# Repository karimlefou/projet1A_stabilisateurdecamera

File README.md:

# Projet 1A : Stabilisateur Brushless

**Équipe** : karim OUERFELLI + AMR  
**Encadrant** : M. Dumas

## 📌 Contexte
Stabilisation  d'un axe pour caméras légères (<1kg) utilisant des moteurs brushless.

## 🛠 Solution
- **Moteurs** : T-Motor MN3508  
- **Contrôle** : STM32 + IMU MPU-6050  
- **Algo** : PID temps-réel (<50ms)

## 🔗 Ressources
[Présentation](https://lien.canva) | [Rapport](https://lien.doc)

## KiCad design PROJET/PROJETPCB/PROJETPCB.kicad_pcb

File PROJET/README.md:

# PROJET
projet de 1 ére année à l'ensea

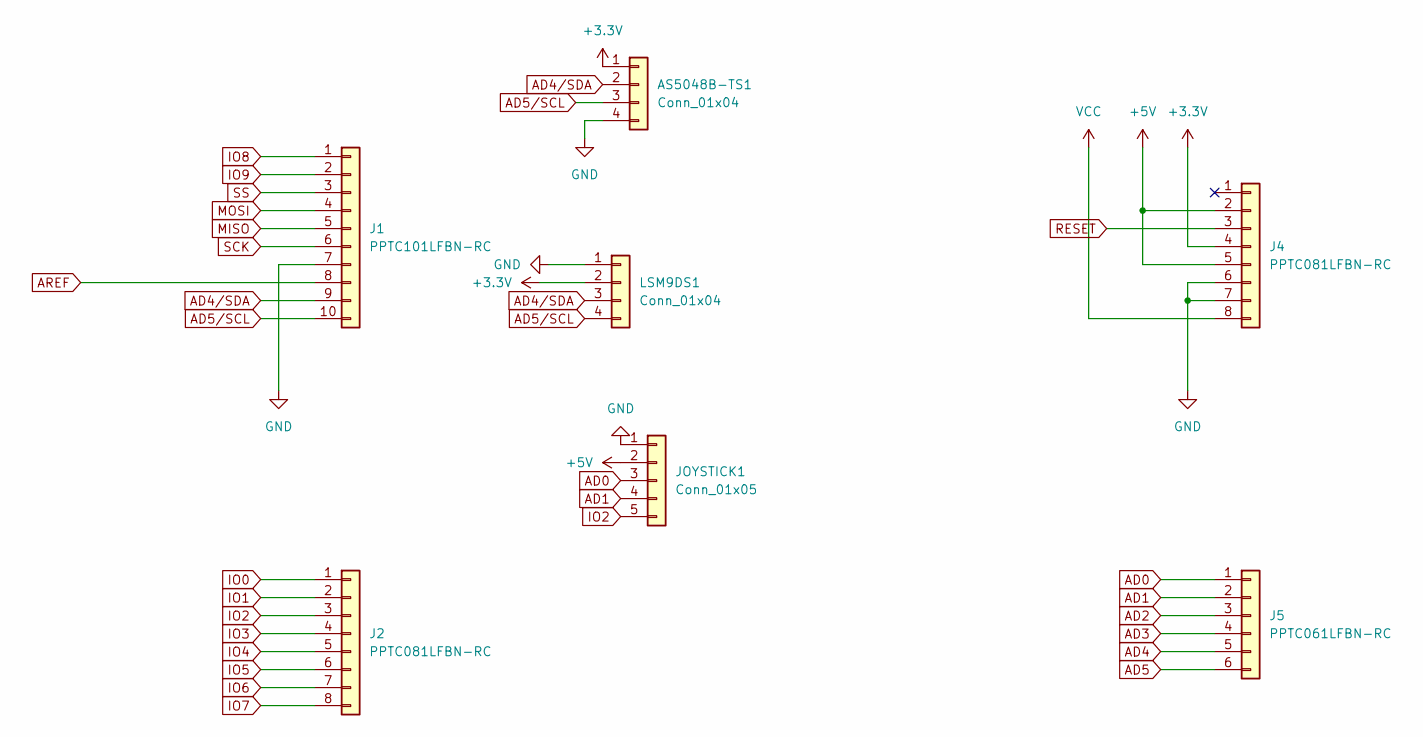
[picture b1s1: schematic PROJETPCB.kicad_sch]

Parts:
AS5048B-TS1: Conn_01x04; JST_XA_B04B-XASK-1_1x04_P2.50mm_Vertical
J1: PPTC101LFBN-RC; PinSocket_1x10_P2.54mm_Vertical
J2, J4: PPTC081LFBN-RC; PinSocket_1x08_P2.54mm_Vertical
J5: PPTC061LFBN-RC; PinSocket_1x06_P2.54mm_Vertical
JOYSTICK1: Conn_01x05; JST_EH_S5B-EH_1x05_P2.50mm_Horizontal
LSM9DS1: Conn_01x04; JST_XA_B04B-XASK-1_1x04_P2.50mm_Vertical

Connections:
+3.3V: AS5048B-TS1.1, J4.4, LSM9DS1.2
+5V: J4.2, J4.5, JOYSTICK1.2
AD0: J5.1, JOYSTICK1.3
AD1: J5.2, JOYSTICK1.4
AD2: J5.3
AD3: J5.4
AD4: J5.5
AD4/SDA: AS5048B-TS1.2, J1.9, LSM9DS1.3
AD5: J5.6
AD5/SCL: AS5048B-TS1.3, J1.10, LSM9DS1.4
AREF: J1.8
GND: AS5048B-TS1.4, J1.7, J4.6, J4.7, JOYSTICK1.1, LSM9DS1.1
IO0: J2.1
IO1: J2.2
IO2: J2.3, JOYSTICK1.5
IO3: J2.4
IO4: J2.5
IO5: J2.6
IO6: J2.7
IO7: J2.8
IO8: J1.1
IO9: J1.2
MISO: J1.5
MOSI: J1.4
RESET: J4.3
SCK: J1.6
SS: J1.3
VCC: J4.8

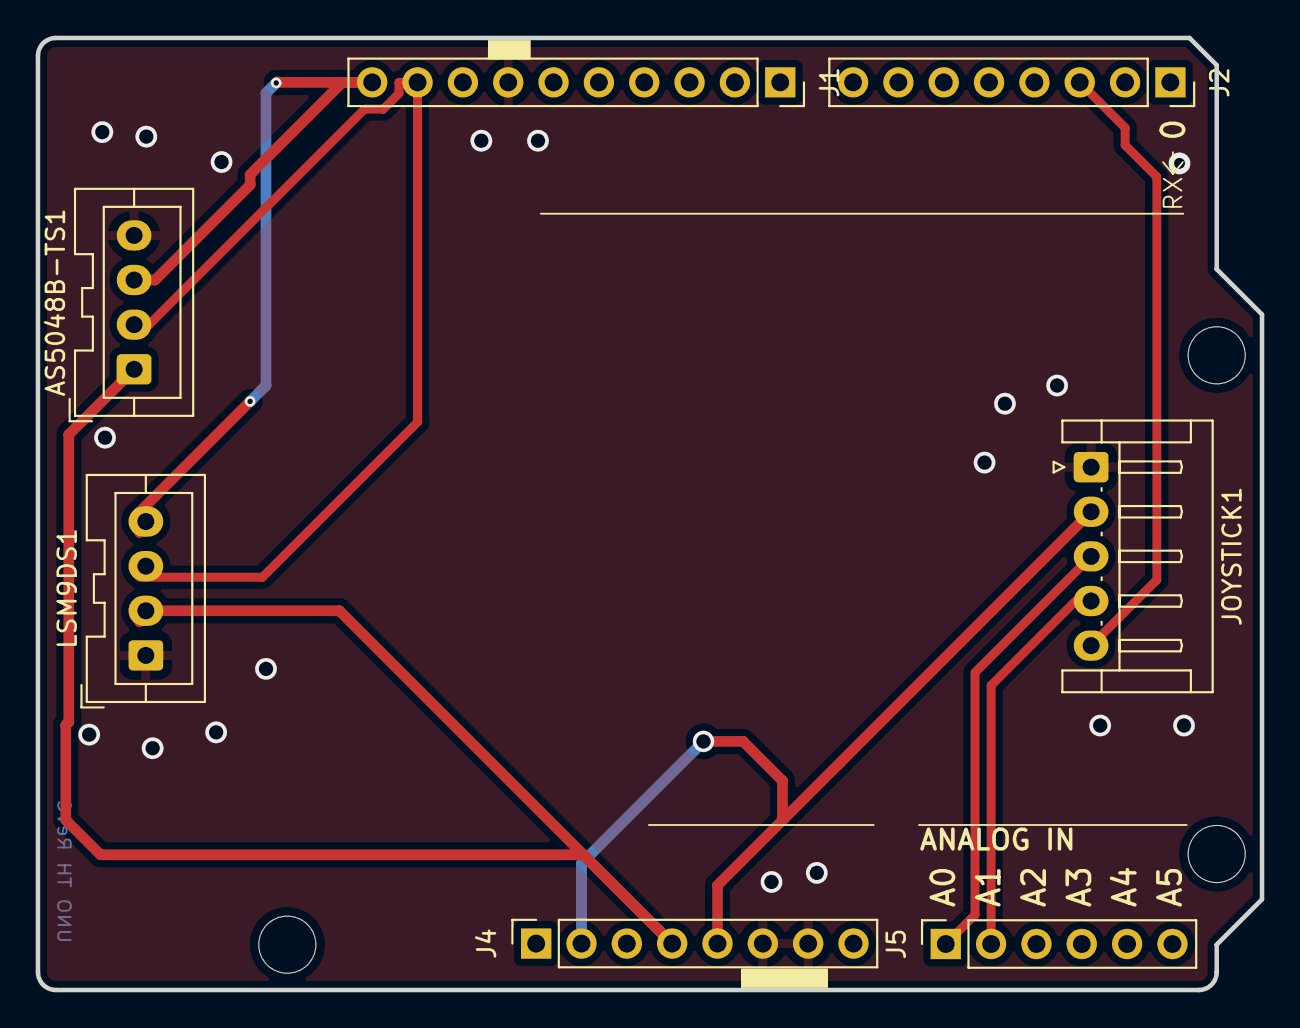
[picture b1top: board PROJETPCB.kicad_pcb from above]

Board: 2 copper layers, 68.6 x 53.3 mm, 7 parts (0 on the bottom side), 8 nets.
